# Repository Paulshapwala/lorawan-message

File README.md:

# lorawan-message

LoRaWAN messaging between end devices through a gateway and a Node-RED router. The prototype is intended for short updates in areas with limited connectivity, such as wildlife conservation teams reporting from a patrol. Coverage depends on the gateway, antenna placement, terrain, and radio link. The gateway needs a connection to the LoRaWAN network server.

```mermaid
flowchart LR
    A["Sending device"] -->|"LoRaWAN uplink"| G["Gateway"]
    G --> T["The Things Stack"]
    T -->|"MQTT"| N["Node-RED router"]
    N -->|"Queue downlink"| T
    T --> G
    G -->|"LoRaWAN downlink"| B["Receiving device"]
```

The sender selects a destination with the P1.0 button and sends a test message or text from a phone over Bluetooth Low Energy (BLE). Node-RED reads the destination tag and queues the message with The Things Stack. The receiving Class A device opens its receive windows when its operator chooses **Check messages** or sends `/poll` from a connected phone. The dashboard shows queue and transmission status. The receiving device displays the text on its OLED and forwards it to a connected phone with UART open.

## Project layout

| Path | Contents |
| --- | --- |
| `networking/src/` | Pro Micro firmware, OLED button menu, radio setup, and saved LoRaWAN session |
| `networking/node-red/ttn-routing.json` | Bidirectional router and FlowFuse Dashboard |
| `networking/ttn/decode_uplink.js` | Optional TTN uplink formatter |
| `hardware/` | KiCad schematic and PCB reference for the prototype |

## Set up two devices

1. Register `custom-1` and `custom-2` as LoRaWAN 1.0.x Class A ABP devices in the same TTN application. The included firmware targets the EU868 frequency plan. Match each device's initial RX1 delay and RX2 data rate to its settings in `networking/platformio.ini`. See the [TTN ABP setup guide](https://www.thethingsindustries.com/docs/hardware/devices/adding-devices/manual/abp/).
2. Create an `end devices` folder beside `networking`. Make a copy of `networking/device.example.json` named `custom-1.json` and another named `custom-2.json` in that folder. Set each device ID and enter its own TTN values as hex strings without spaces. Git ignores the credentials folder.
3. Open `networking` in PlatformIO. Upload `gateway_connect` to the first board and `gateway_connect_custom_2` to the second board. Use `promicro_nrf52840` for an OLED bench test or `hello_ble` to test the BLE UART echo.

## Set up Node-RED

1. Install [FlowFuse Dashboard](https://dashboard.flowfuse.com/getting-started.html) in Node-RED.
2. Replace every occurrence of `your-ttn-app` in the exported flow with your TTN application ID before importing it. The export is configured for TTN EU1. If your application uses another cluster, also update the MQTT host, TLS server name, and queue API host to match.
3. Edit the MQTT broker's **Security** settings. Use `<application-id>@ttn` as the username and your TTN application API key as the password. Set the same key as the bearer token on **Queue downlink in TTN**. The key needs access to read application traffic and write downlinks. [TTN MQTT setup](https://www.thethingsindustries.com/docs/integrations/other-integrations/mqtt/)
4. Deploy the flow and open [the communications dashboard](http://localhost:1880/dashboard/communications). Optionally copy the uplink formatter into the TTN application.

## Send and receive

- Tap **P1.0** to scroll. Hold it for about 0.7 seconds to select.
- Choose **Change target** and select a device, then choose **Send hello**. The selected target is saved on the board.
- Wait for the dashboard to show the message queued, then choose **Check messages** on the receiving device. Use **Back** to return to the action menu.
- To add a device, register its ID in the TTN application, add it to `custom_end_devices` in `platformio.ini`, and rebuild the relevant boards. Give the new board its own PlatformIO profile and credential file.

### Send from a phone

1. Set the destination using **Change target**, then hold P1.0 on **BLE Control**. The board advertises for 60 seconds under a name such as `custom-1 BLE`.
2. Connect from Bluefruit LE Connect and open **UART**. Enter the pairing code shown on the OLED when prompted. Use **Back** to return to the action menu while keeping the phone connected. [Adafruit UART Terminal guide](https://learn.adafruit.com/bluefruit-le-connect/uart-terminal)
3. Type a line of up to 48 bytes and tap **Send**. Once the dashboard shows **Queued**, choose **Check messages** on the receiver or send `/poll` from its phone. Choose **Turn BLE off** in **BLE Control** to disconnect the phone.

## Message format

| Direction | FPort | Payload |
| --- | --- | --- |
| Routed uplink | 2 | One destination byte followed by message bytes |
| Poll uplink | 1 | Short poll message that opens receive windows |
| Application downlink | 1 | Message bytes forwarded to the selected device |

The tag is the decimal suffix of the device ID stored in a byte. For example, `0x02` maps to `custom-2`. The supported IDs are `custom-1` through `custom-255`. Application downlinks use the receiving device's downlink budget. Check your [network and regional airtime limits](https://www.thethingsnetwork.org/docs/lorawan/duty-cycle/) when planning field tests.

## Hardware attribution

The KiCad files in `hardware/` contain my modifications to gargomoma’s FakeTec PCB for this prototype. [Original FakeTec hardware repository](https://github.com/gargomoma/fakeTec_pcb)

I develop the modified schematic and PCB in a separate repository. [Active Meshtastic Node hardware project](https://github.com/Paulshapwala/meshtastic-node)

## Prototype wiring

The current board uses a Pro Micro nRF52840, an RA-01SH LoRa module, and an SSD1306 I²C OLED at `0x3C`.

| Signal | Pro Micro GPIO |
| --- | --- |
| OLED SDA / SCL | P1.04 / P0.11 |
| RA-01SH NSS / SCK | P1.13 / P1.11 |
| RA-01SH MOSI / MISO | P1.15 / P0.02 |
| RA-01SH DIO1 / RESET / BUSY | P0.10 / P0.09 / P0.29 |
| RA-01SH RXEN | P0.17 |
| User button | P1.00 with an active-low switch to ground |
| Switched 3.3 V enable | P0.13 |

The prototype connects the radio's DIO2 to its TXEN line. The PCB source includes its placed footprints. Editing the design with replacement parts may require the original custom footprint libraries.

## Contributing

Issues and pull requests are welcome. When sharing a bug report or change, include the board profile and what you tested. Use the Meshtastic Node hardware repository for work on the PCB. [Project issues](https://github.com/Paulshapwala/lorawan-message/issues)

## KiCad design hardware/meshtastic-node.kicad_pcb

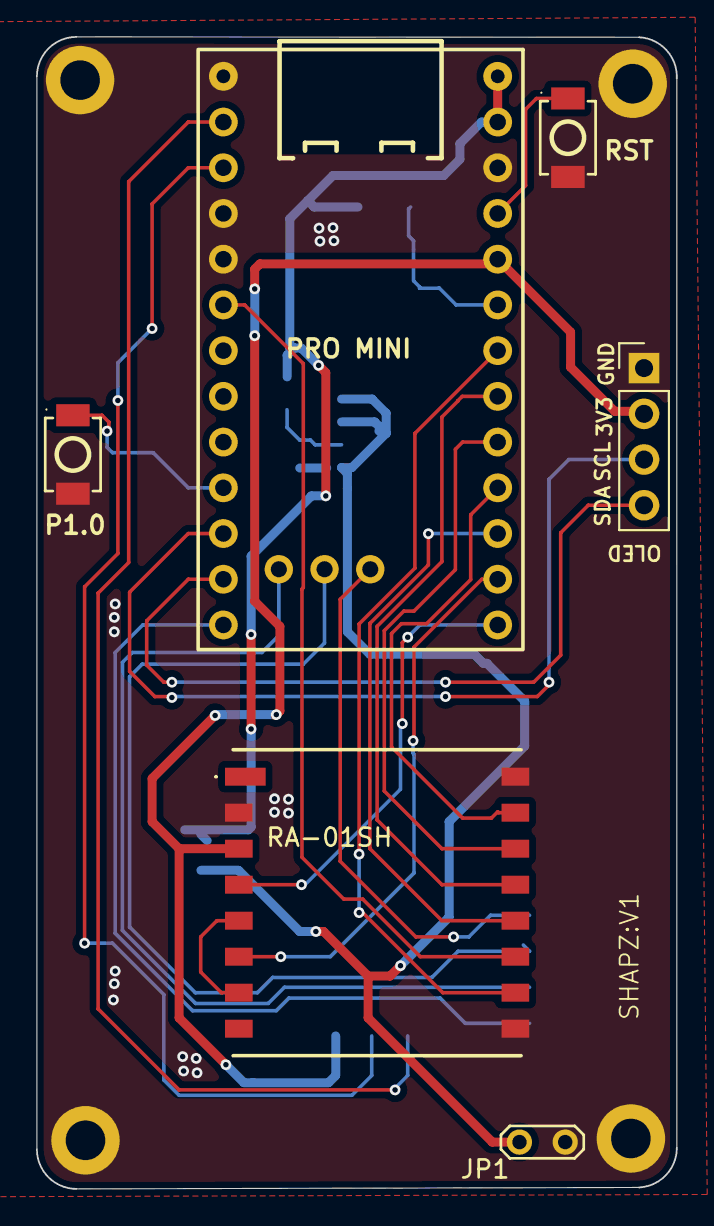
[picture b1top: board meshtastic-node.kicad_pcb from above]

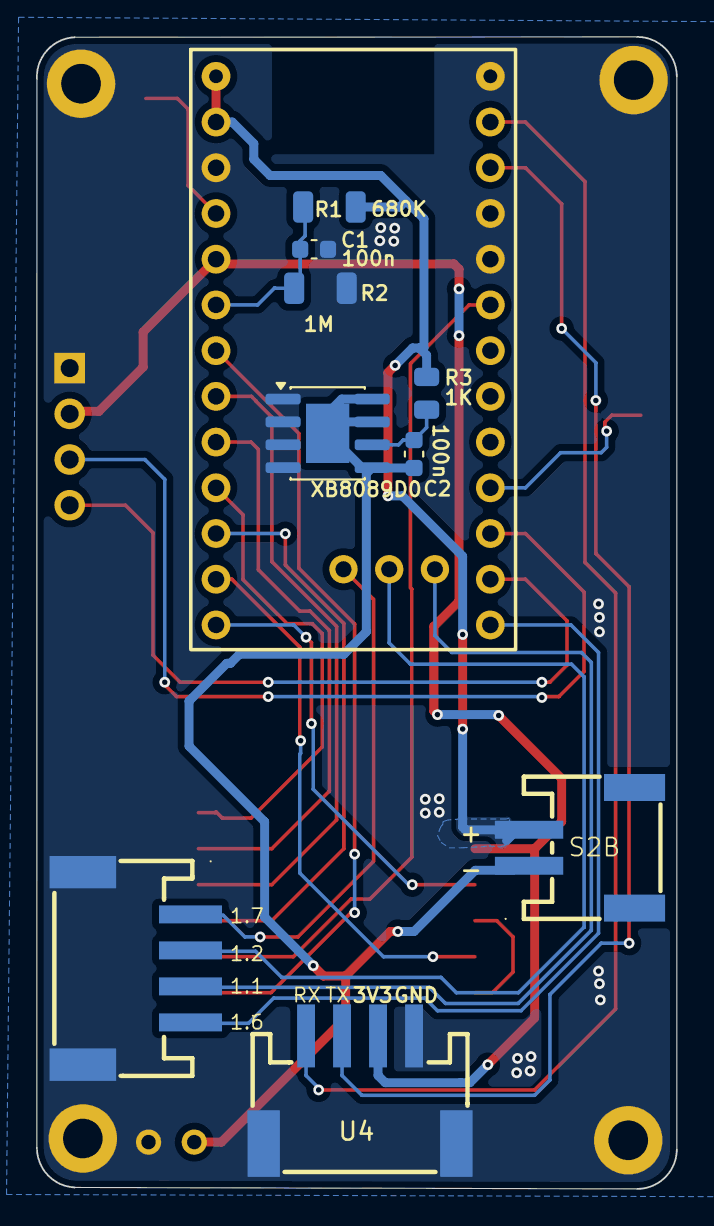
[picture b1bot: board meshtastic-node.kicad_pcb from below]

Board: 2 copper layers, 35.6 x 64.0 mm, 19 parts (9 on the bottom side), 25 nets.

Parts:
C1, C2: 100nF; C_0603_1608Metric
H1, H2, H3, H4: MountingHole_Pad; MountingHole_2.2mm_M2_DIN965_Pad
IC1: RA-01SH; RA01SH
J1: Conn_02x01_MountingPin; CONN-SMD_P2.00_S2B-PH-SM4-TB-LF-SN
J2: Conn_01x04_Pin; PinHeader_1x04_P2.54mm_Vertical
JP1: Jumper_2_Open; TestPoint_2Pads_Pitch2.54mm_Drill0.8mm
R1: 680K; R_1206
R2: 1.0M; R_1206
R3: 1k; R_0805
SW1, SW2: SW_Push; SW-SMD_L3.9-W3.0-P4.45
U1: nice!nano_v2; SuperMini NRF52840
U2: XB8089D0; SOIC-8-1EP_3.9x4.9mm_P1.27mm_EP2.41x3.3mm
U3, U4: S4B-PH-SM4-TB; CONN-SMD_S4B-PH-SM4-TB-LF-SN

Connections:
+3V3: IC1.3 (3.3V), J2.2, U1.21 (3.3v), U4.3
+BATT: J1.2, R1.1, R3.1, U1.24 (BAT+), U1.25 (BAT+)
-BATT: C2.1, J1.1, JP1.2 (B), U2.5 (GND), U2.7 (GND), U2.8 (GND), U2.9 (EPAD)
/BTN: SW2.2, U1.9 (P1.00)
/BUSY: IC1.10 (BUSY), U1.19 (P0.29)
/Batt%: C1.1, R1.2, R2.1, U1.20 (P0.31)
/CS: IC1.15 (NSS), U1.16 (P1.13)
/DI01: IC1.6 (DIO1), U1.14 (P0.10)
/MISO: IC1.13 (MISO), U1.18 (P0.02)
/MOSI: IC1.14 (MOSI), U1.17 (P1.15)
/P1.1: U1.26 (P1.01), U3.3
/P1.2: U1.27 (P1.02), U3.2
/P1.6: U1.12 (P1.06), U3.4
/P1.7: U1.28 (P1.07), U3.1
/RST: IC1.4 (RESET), U1.13 (P0.09)
/RST_BTN: SW1.2, U1.22 (RST)
/RX: U1.1 (P0.06), U4.1
/RXEN: IC1.11 (RXEN), U1.5 (P0.17)
/SCK: IC1.12 (SCK), U1.15 (P1.11)
/SCL: J2.3, U1.10 (P0.11)
/SDA: J2.4, U1.11 (P1.04)
/TX: U1.2 (P0.08), U4.2
GND: C1.2, H1.1 (1_1), H2.1 (1_1), H3.1 (1_1), H4.1 (1_1), IC1.2 (GND_1), IC1.9 (GND_2), IC1.16 (GND_3), J2.1, JP1.1 (A), R2.2, SW1.1, SW2.1, U1.0 (GND), U1.3 (GND), U1.4 (GND), U1.23 (GND), U2.1 (VM), U2.2 (VM), U2.3 (VM), U2.4 (VM), U3.5, U3.6, U4.4, U4.5, U4.6
unnamed: IC1.5 (TXEN), IC1.7 (DIO2)
unnamed: C2.2, R3.2, U2.6 (VDD)
